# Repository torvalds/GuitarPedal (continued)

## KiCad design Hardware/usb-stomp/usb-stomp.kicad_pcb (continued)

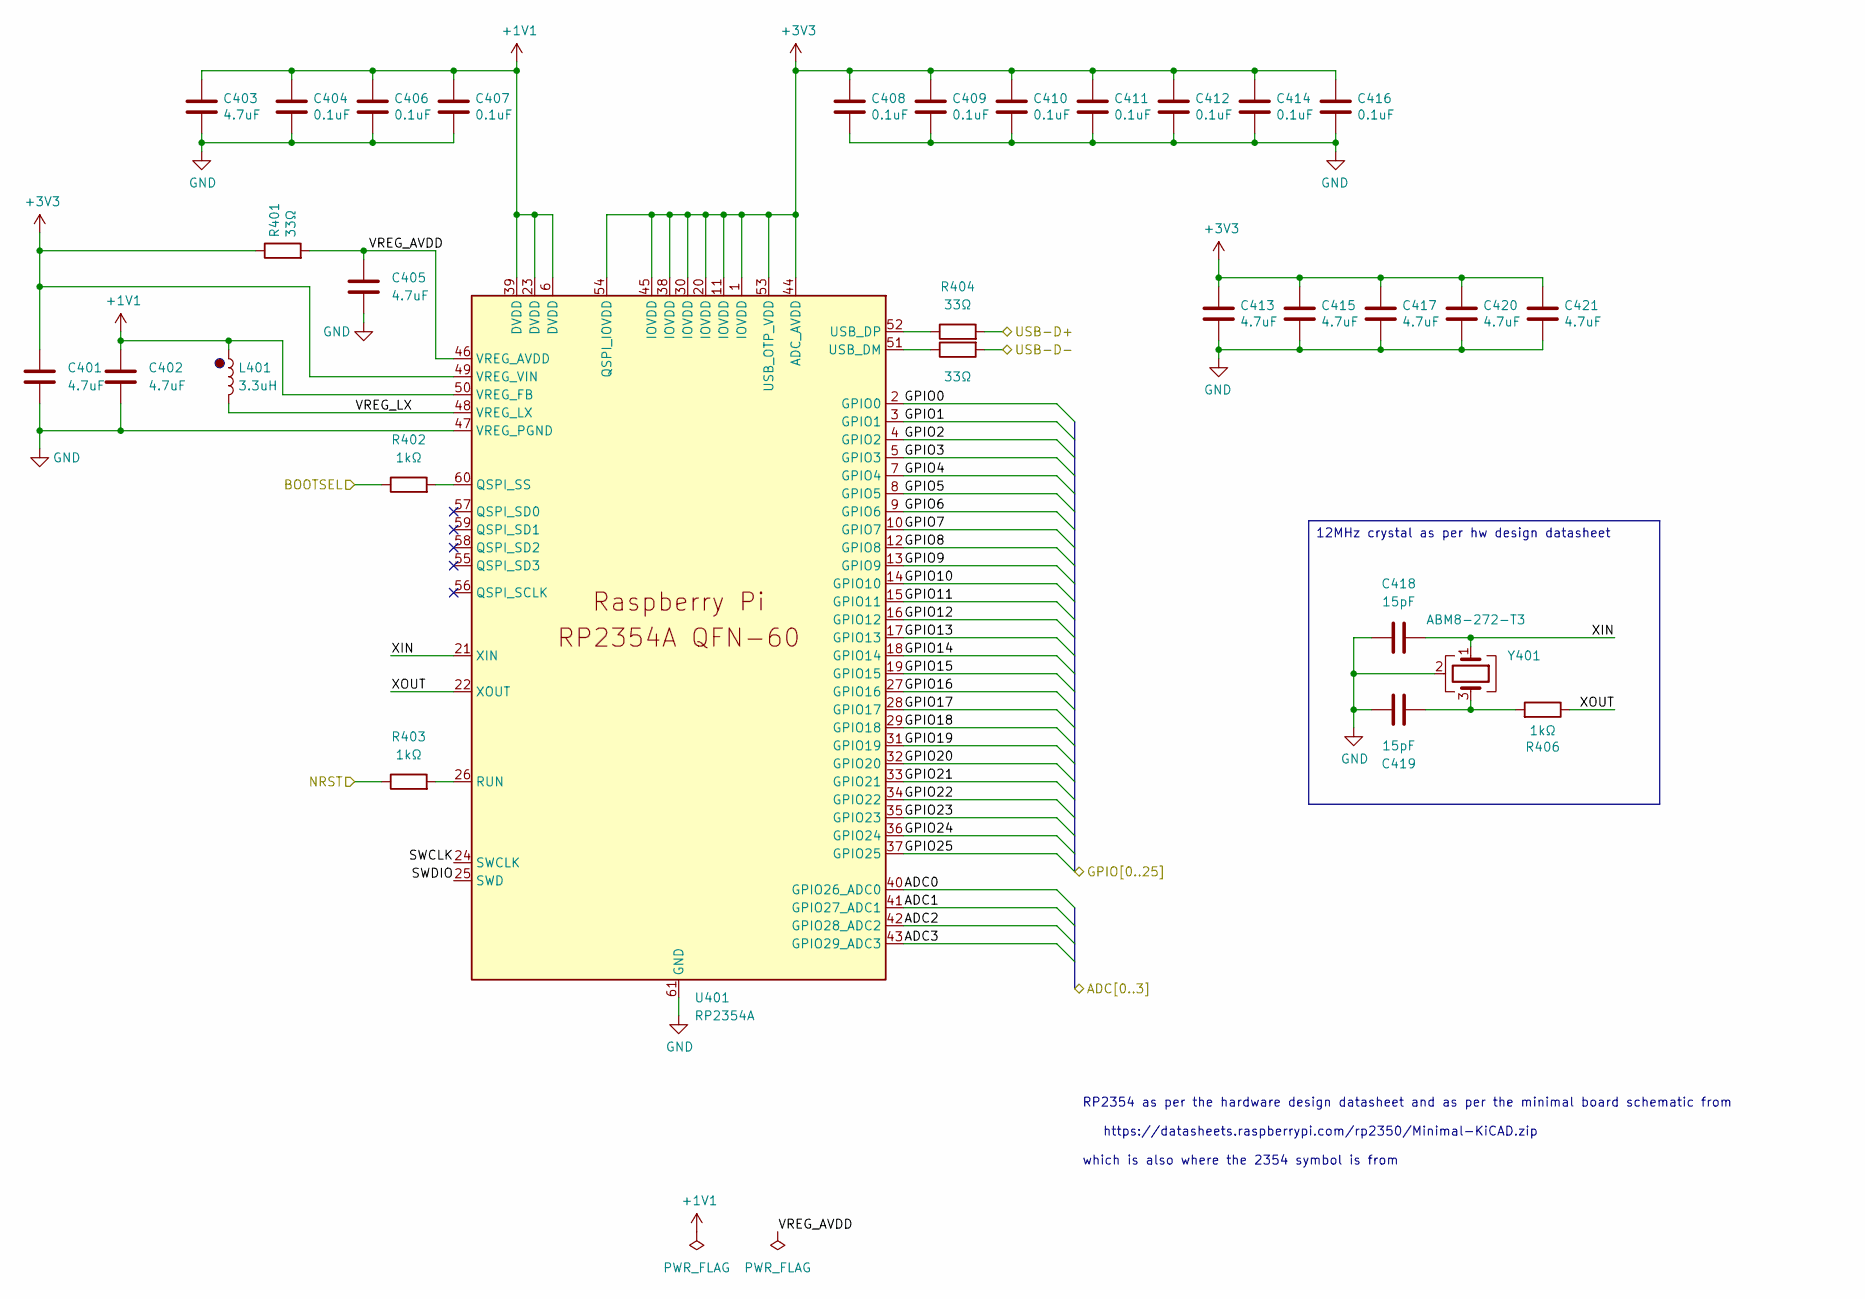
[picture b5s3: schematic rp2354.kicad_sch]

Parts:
C401, C402, C403, C405, C413, C415, C417, C420, C421: 4.7uF; C_0402_1005Metric; MANUFACTURER_PART_NUMBER GRM155R61E475ME15D; LCSC PN C2858031
C404, C406, C407, C408, C409, C410, C411, C412, C414, C416: 0.1uF; C_0402_1005Metric; MANUFACTURER_PART_NUMBER CL05B104KO5NNNC; LCSC PN C1525
C418, C419: 15pF; C_0402_1005Metric; MANUFACTURER_PART_NUMBER GRM1555C1H150JA01D; LCSC PN C76950
L401: 3.3uH; AOTA-B2016; MANUFACTURER_PART_NUMBER AOTA-B201610S3R3-101-T; LCSC PN C42411119
R401, R404, R405: 33Ω; R_0402_1005Metric; MANUFACTURER_PART_NUMBER 0402WGF330JTCE; LCSC PN C25105
R402, R403, R406: 1kΩ; R_0402_1005Metric; MANUFACTURER_PART_NUMBER 0402WGF1001TCE; LCSC PN C11702
U401: RP2354A; QFN-60-1EP_7x7mm_P0.4mm_EP3.4x3.4mm_ThermalVias; MANUFACTURER_PART_NUMBER RP2354A; LCSC PN C41378174
Y401: ABM8-272-T3; Crystal_SMD_3225-4Pin_3.2x2.5mm; MANUFACTURER_PART_NUMBER ABM8-272-T3; LCSC PN C20625731

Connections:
+1V1: C402.1, C403.1, C404.1, C406.1, C407.1, L401.1, U401.6 (DVDD), U401.23 (DVDD), U401.39 (DVDD), U401.50 (VREG_FB)
+3V3: C401.1, C408.1, C409.1, C410.1, C411.1, C412.1, C413.1, C414.1, C415.1, C416.1, C417.1, C420.1, C421.1, R401.1, U401.1 (IOVDD), U401.11 (IOVDD), U401.20 (IOVDD), U401.30 (IOVDD), U401.38 (IOVDD), U401.44 (ADC_AVDD), U401.45 (IOVDD), U401.49 (VREG_VIN), U401.53 (USB_OTP_VDD), U401.54 (QSPI_IOVDD); also elsewhere on the board
/BOOTSEL: R402.1; also elsewhere on the board
/RP2354/ADC0: U401.40 (GPIO26_ADC0); also elsewhere on the board
/RP2354/ADC1: U401.41 (GPIO27_ADC1); also elsewhere on the board
/RP2354/ADC2: U401.42 (GPIO28_ADC2)
/RP2354/ADC3: U401.43 (GPIO29_ADC3)
/RP2354/GPIO0: U401.2 (GPIO0); also elsewhere on the board
/RP2354/GPIO1: U401.3 (GPIO1)
/RP2354/GPIO2: U401.4 (GPIO2)
/RP2354/GPIO3: U401.5 (GPIO3)
/RP2354/GPIO4: U401.7 (GPIO4)
/RP2354/GPIO5: U401.8 (GPIO5)
/RP2354/GPIO6: U401.9 (GPIO6)
/RP2354/GPIO7: U401.10 (GPIO7)
/RP2354/GPIO12: U401.16 (GPIO12); also elsewhere on the board
/RP2354/GPIO13: U401.17 (GPIO13); also elsewhere on the board
/RP2354/GPIO14: U401.18 (GPIO14); also elsewhere on the board
/RP2354/GPIO15: U401.19 (GPIO15)
/RP2354/GPIO16: U401.27 (GPIO16)
/RP2354/GPIO17: U401.28 (GPIO17)
/RP2354/GPIO18: U401.29 (GPIO18)
/RP2354/GPIO19: U401.31 (GPIO19)
/RP2354/GPIO20: U401.32 (GPIO20); also elsewhere on the board
/RP2354/GPIO21: U401.33 (GPIO21); also elsewhere on the board
/RP2354/GPIO22: U401.34 (GPIO22)
/RP2354/GPIO23: U401.35 (GPIO23)
/RP2354/GPIO24: U401.36 (GPIO24)
/RP2354/GPIO25: U401.37 (GPIO25); also elsewhere on the board
/RP2354/NRST: R403.1
/RP2354/SWCLK: U401.24 (SWCLK)
/RP2354/SWDIO: U401.25 (SWD)
/RP2354/VREG_AVDD: C405.1, R401.2, U401.46 (VREG_AVDD)
/RP2354/VREG_LX: L401.2, U401.48 (VREG_LX)
/RP2354/XIN: C418.1, U401.21 (XIN), Y401.1
/RP2354/XOUT: R406.1, U401.22 (XOUT)
/TAC5242/I2S.BCLK: U401.12 (GPIO8); also elsewhere on the board
/TAC5242/I2S.DIN: U401.14 (GPIO10); also elsewhere on the board
/TAC5242/I2S.DOUT: U401.15 (GPIO11); also elsewhere on the board
/TAC5242/I2S.FSYNC: U401.13 (GPIO9); also elsewhere on the board
/USB-D+: R404.2; also elsewhere on the board
/USB-D-: R405.2; also elsewhere on the board
GND: C401.2, C402.2, C403.2, C404.2, C405.2, C406.2, C407.2, C408.2, C409.2, C410.2, C411.2, C412.2, C413.2, C414.2, C415.2, C416.2, C417.2, C418.2, C419.2, C420.2, C421.2, U401.47 (VREG_PGND), U401.61 (GND), Y401.2 (G), Y401.4 (G); also elsewhere on the board
unnamed: C419.1, R406.2, Y401.3
unnamed: R402.2, U401.60 (QSPI_SS)
unnamed: R403.2, U401.26 (RUN)
unnamed: R405.1, U401.51 (USB_DM)
unnamed: R404.1, U401.52 (USB_DP)

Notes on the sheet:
RP2354 as per the hardware design datasheet and as per the minimal board schematic from https://datasheets.raspberrypi.com/rp2350/Minimal-KiCAD.zip which is also where the 2354 symbol is from
12MHz crystal as per hw design datasheet

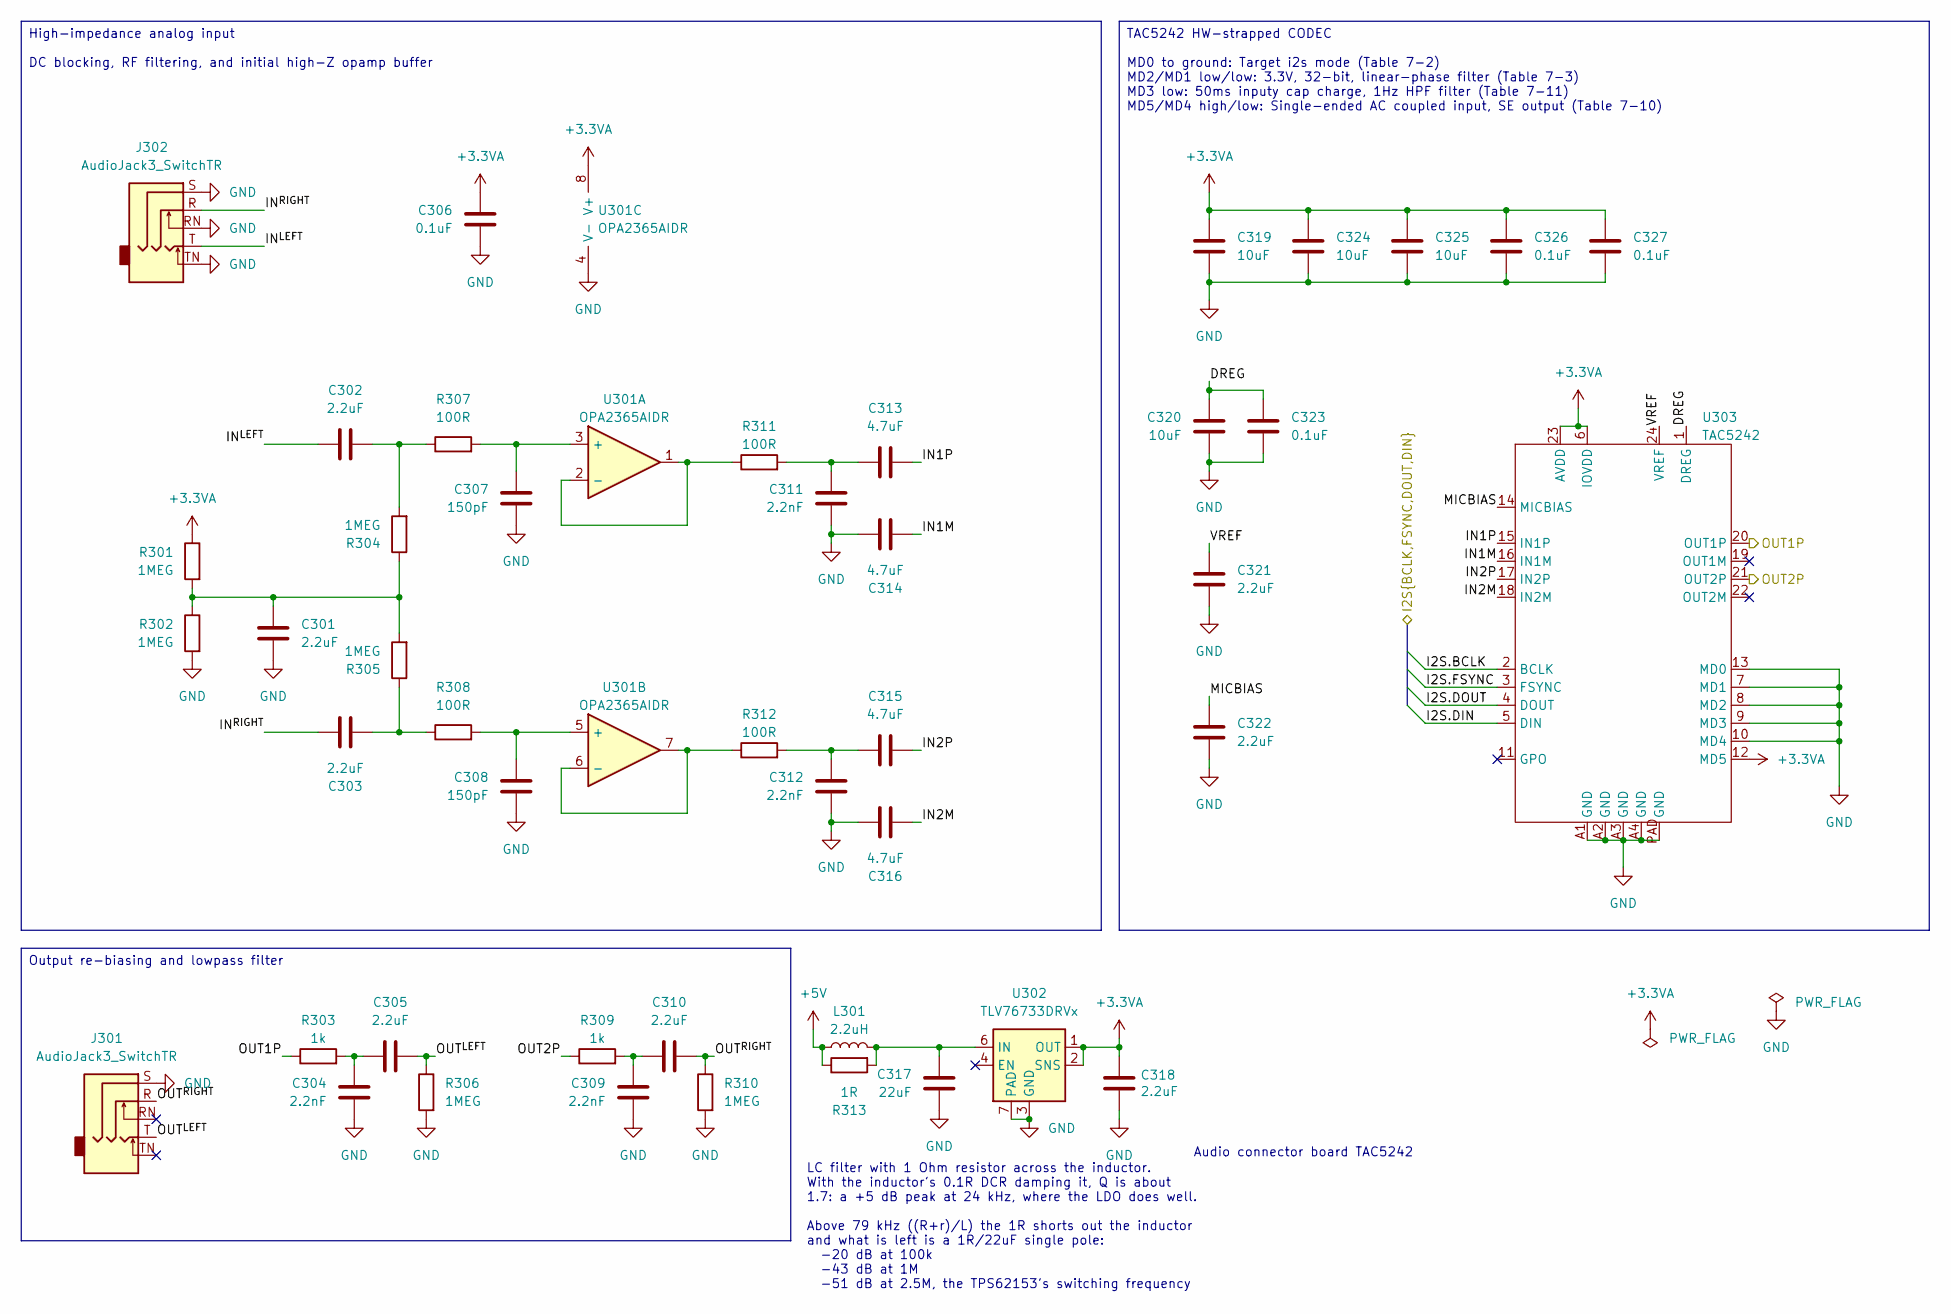
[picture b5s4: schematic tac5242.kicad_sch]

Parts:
C301, C302, C303, C305, C310, C318, C321, C322: 2.2uF; C_0603_1608Metric; MANUFACTURER_PART_NUMBER GRM188Z71E225KE43D; LCSC PN C415535
C304, C309, C311, C312: 2.2nF; C_0402_1005Metric; MANUFACTURER_PART_NUMBER GRM1555C1H222GA01D; LCSC PN C2987940
C306, C323, C326, C327: 0.1uF; C_0402_1005Metric; MANUFACTURER_PART_NUMBER CL05B104KO5NNNC; LCSC PN C1525
C307, C308: 150pF; C_0402_1005Metric; MANUFACTURER_PART_NUMBER GRM1555C1E151JA01D; LCSC PN C710836
C313, C314, C315, C316: 4.7uF; C_0805_2012Metric; MANUFACTURER_PART_NUMBER GRM21BZ71H475KE15L; LCSC PN C437557
C317: 22uF; C_1210_3225Metric; MANUFACTURER_PART_NUMBER CL32B226KAJNNNE; LCSC PN C309062
C319, C320, C324, C325: 10uF; C_0603_1608Metric; MANUFACTURER_PART_NUMBER GRM188R61E106MA73D; LCSC PN C91606
J301, J302: AudioJack3_SwitchTR; NRJ6HM-1-PRE
L301: 2.2uH; L_0806; MANUFACTURER_PART_NUMBER DFE201612E-2R2M=P2; LCSC PN C337893
R301, R302, R304, R305, R306, R310: 1MEG; R_0402_1005Metric; MANUFACTURER_PART_NUMBER MCS04020C1004FE000; LCSC PN C1884615
R303, R309: 1k; R_0402_1005Metric; MANUFACTURER_PART_NUMBER RT0402FRE071KL; LCSC PN C136974
R307, R308, R311, R312: 100R; R_0402_1005Metric; MANUFACTURER_PART_NUMBER RT0402BRD07100RL; LCSC PN C705627
R313: 1R; R_0402_1005Metric; MANUFACTURER_PART_NUMBER FRC0402F1R00TS; LCSC PN C2909329
U301: OPA2365AIDR; SOIC-8_3.9x4.9mm_P1.27mm; MANUFACTURER_PART_NUMBER OPA2365AIDR; LCSC PN C130011
U302: TLV76733DRVx; WSON-6-1EP_2x2mm_P0.65mm_EP1x1.6mm; MANUFACTURER_PART_NUMBER TLV76733DRVR; LCSC PN C2848334
U303: TAC5242; MANUFACTURER_PART_NUMBER TAC5242IRGER; LCSC PN C47122155

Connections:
+3.3VA: C306.2, C318.1, C319.1, C324.1, C325.1, C326.1, C327.1, R301.1, U301.8 (V+), U302.1 (OUT), U302.2 (SNS), U303.6 (IOVDD), U303.12 (MD5), U303.23 (AVDD)
+5V: L301.1, R313.1; also elsewhere on the board
/OUT1P: R303.1, U303.20 (OUT1P)
/OUT2P: R309.1, U303.21 (OUT2P)
/TAC5242/DREG: C320.1, C323.1, U303.1 (DREG)
/TAC5242/I2S.BCLK: U303.2 (BCLK); also elsewhere on the board
/TAC5242/I2S.DIN: U303.5 (DIN); also elsewhere on the board
/TAC5242/I2S.DOUT: U303.4 (DOUT); also elsewhere on the board
/TAC5242/I2S.FSYNC: U303.3 (FSYNC); also elsewhere on the board
/TAC5242/IN1M: C314.2, U303.16 (IN1M)
/TAC5242/IN1P: C313.2, U303.15 (IN1P)
/TAC5242/IN2M: C316.2, U303.18 (IN2M)
/TAC5242/IN2P: C315.2, U303.17 (IN2P)
/TAC5242/IN^{LEFT}: C302.1, J302.T
/TAC5242/IN^{RIGHT}: C303.1, J302.R
/TAC5242/MICBIAS: C322.1, U303.14 (MICBIAS)
/TAC5242/OUT^{LEFT}: C305.2, J301.T, R306.1
/TAC5242/OUT^{RIGHT}: C310.2, J301.R, R310.1
/TAC5242/VREF: C321.1, U303.24 (VREF)
GND: C301.1, C304.1, C306.1, C307.2, C308.2, C309.1, C311.1, C312.1, C314.1, C316.1, C317.2, C318.2, C319.2, C320.2, C321.2, C322.2, C323.2, C324.2, C325.2, C326.2, C327.2, J301.S, J302.RN, J302.S, J302.TN, R302.2, R306.2, R310.2, U301.4 (V-), U302.3 (GND), U302.5 (GND), U302.7 (PAD), U303.7 (MD1), U303.8 (MD2), U303.9 (MD3), U303.10 (MD4), U303.13 (MD0), U303.A1 (GND), U303.A2 (GND), U303.A3 (GND), U303.A4 (GND), U303.PAD (GND); also elsewhere on the board
unnamed: C301.2, R301.2, R302.1, R304.1, R305.2
unnamed: C302.2, R304.2, R307.1
unnamed: C303.2, R305.1, R308.1
unnamed: C304.2, C305.1, R303.2
unnamed: C309.2, C310.1, R309.2
unnamed: C311.2, C313.1, R311.2
unnamed: C312.2, C315.1, R312.2
unnamed: C307.1, R307.2, U301.3 (+)
unnamed: R311.1, U301.1, U301.2 (-)
unnamed: C308.1, R308.2, U301.5 (+)
unnamed: R312.1, U301.6 (-), U301.7
unnamed: C317.1, L301.2, R313.2, U302.6 (IN)

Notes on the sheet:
LC filter with 1 Ohm resistor across the inductor. With the inductor's 0.1R DCR damping it, Q is about 1.7: a +5 dB peak at 24 kHz, where the LDO does well. Above 79 kHz ((R+r)/L) the 1R shorts out the inductor and what is left is a 1R/22uF single pole: -20 dB at 100k -43 dB at 1M -51 dB at 2.5M, t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
Audio connector board TAC5242
High-impedance analog input DC blocking, RF filtering, and initial high-Z opamp buffer
Output re-biasing and lowpass filter
TAC5242 HW-strapped CODEC MD0 to ground: Target i2s mode (Table 7-2) MD2/MD1 low/low: 3.3V, 32-bit, linear-phase filter (Table 7-3) MD3 low: 50ms inputy cap charge, 1Hz HPF filter (Table 7-11) MD5/MD4 high/low: Single-ended AC coupled input, SE output (Table 7-10)

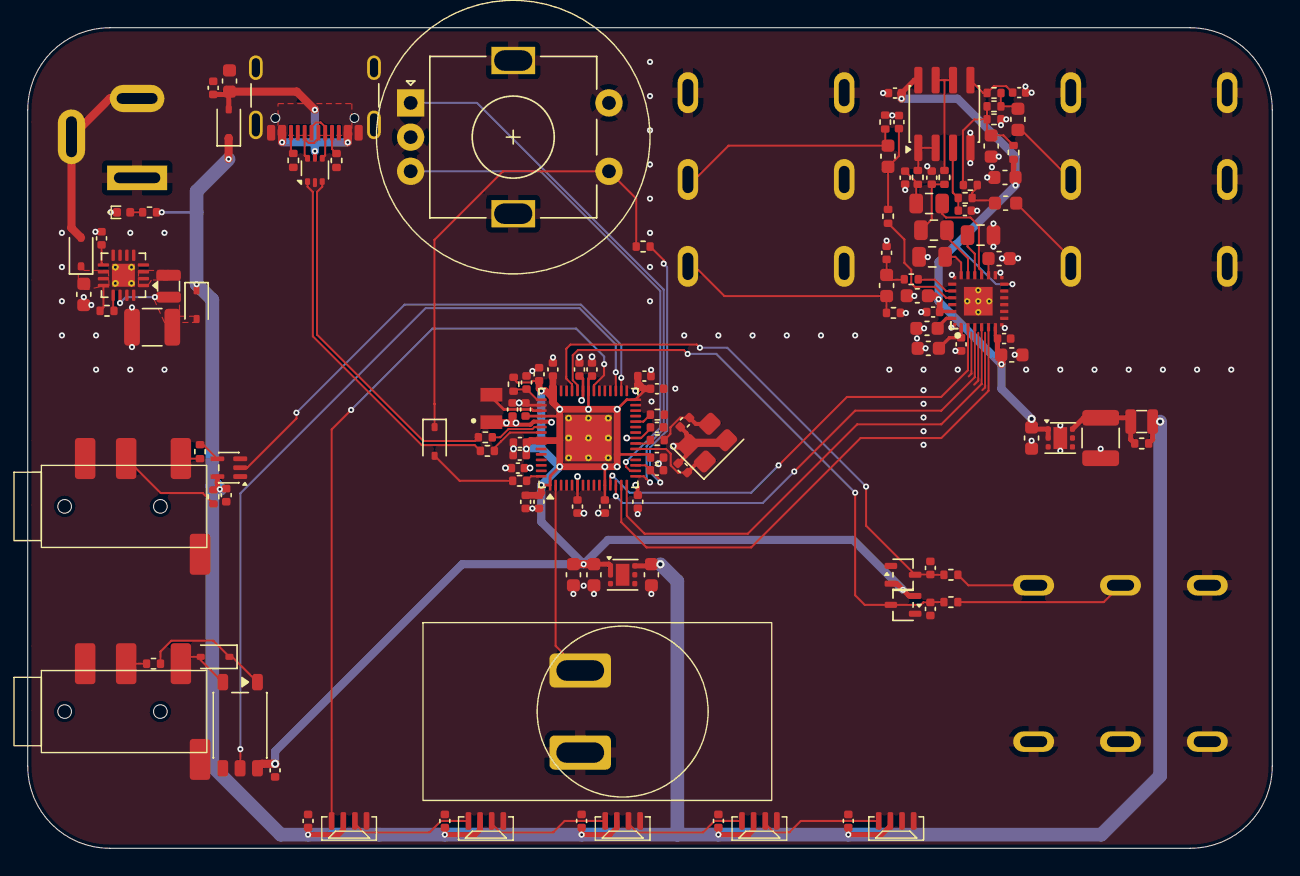
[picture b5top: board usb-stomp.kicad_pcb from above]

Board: 4 copper layers, 91.0 x 60.0 mm, 130 parts (0 on the bottom side), 80 nets.

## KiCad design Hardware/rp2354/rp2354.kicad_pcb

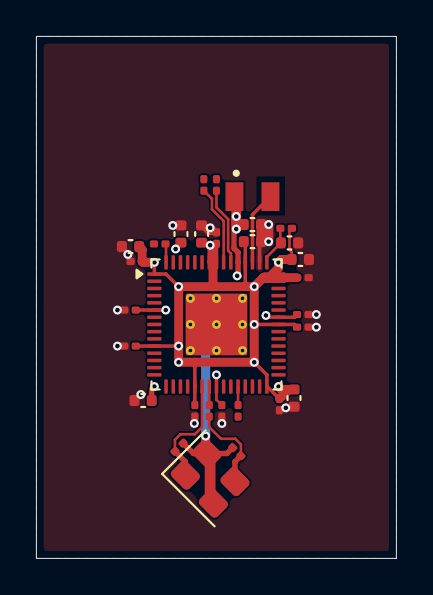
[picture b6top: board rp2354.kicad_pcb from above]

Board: 4 copper layers, 20.0 x 29.0 mm, 30 parts (0 on the bottom side), 12 nets.

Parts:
C1, C2, C3, C5, C17, C18, C19, C20, C21: 4.7uF; C_0402_1005Metric
C4, C6, C7, C8, C9, C10, C11, C12, C13, C14: 0.1uF; C_0201_0603Metric
C15, C16: 15pF; C_0201_0603Metric
L1: 3.3uH; AOTA-B2016
R1, R4, R5: 33R; R_0201_0603Metric
R2, R3, R6: 1k; R_0201_0603Metric
U1: RP2354A; QFN-60-1EP_7x7mm_P0.4mm_EP3.4x3.4mm_ThermalVias
Y1: ABM8-272-T3; Crystal_SMD_3225-4Pin_3.2x2.5mm

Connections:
+1V1: C2.1, C3.1, C4.1, C6.1, C7.1, L1.1, U1.6 (DVDD), U1.23 (DVDD), U1.39 (DVDD), U1.50 (VREG_FB)
+3V3: C1.1, C8.1, C9.1, C10.1, C11.1, C12.1, C13.1, C14.1, C17.1, C18.1, C19.1, C20.1, C21.1, R1.1, U1.1 (IOVDD), U1.11 (IOVDD), U1.20 (IOVDD), U1.30 (IOVDD), U1.38 (IOVDD), U1.44 (ADC_AVDD), U1.45 (IOVDD), U1.49 (VREG_VIN), U1.53 (USB_OTP_VDD), U1.54 (QSPI_IOVDD)
/VREG_AVDD: C5.1, R1.2, U1.46 (VREG_AVDD)
/VREG_LX: L1.2, U1.48 (VREG_LX)
/XIN: C15.1, U1.21 (XIN), Y1.1
/XOUT: R6.1, U1.22 (XOUT)
GND: C1.2, C2.2, C3.2, C4.2, C5.2, C6.2, C7.2, C8.2, C9.2, C10.2, C11.2, C12.2, C13.2, C14.2, C15.2, C16.2, C17.2, C18.2, C19.2, C20.2, C21.2, U1.47 (VREG_PGND), U1.61 (GND), Y1.2 (G), Y1.4 (G)
unnamed: C16.1, R6.2, Y1.3
unnamed: R2.2, U1.60 (QSPI_SS)
unnamed: R3.2, U1.26 (RUN)
unnamed: R5.1, U1.51 (USB_DM)
unnamed: R4.1, U1.52 (USB_DP)

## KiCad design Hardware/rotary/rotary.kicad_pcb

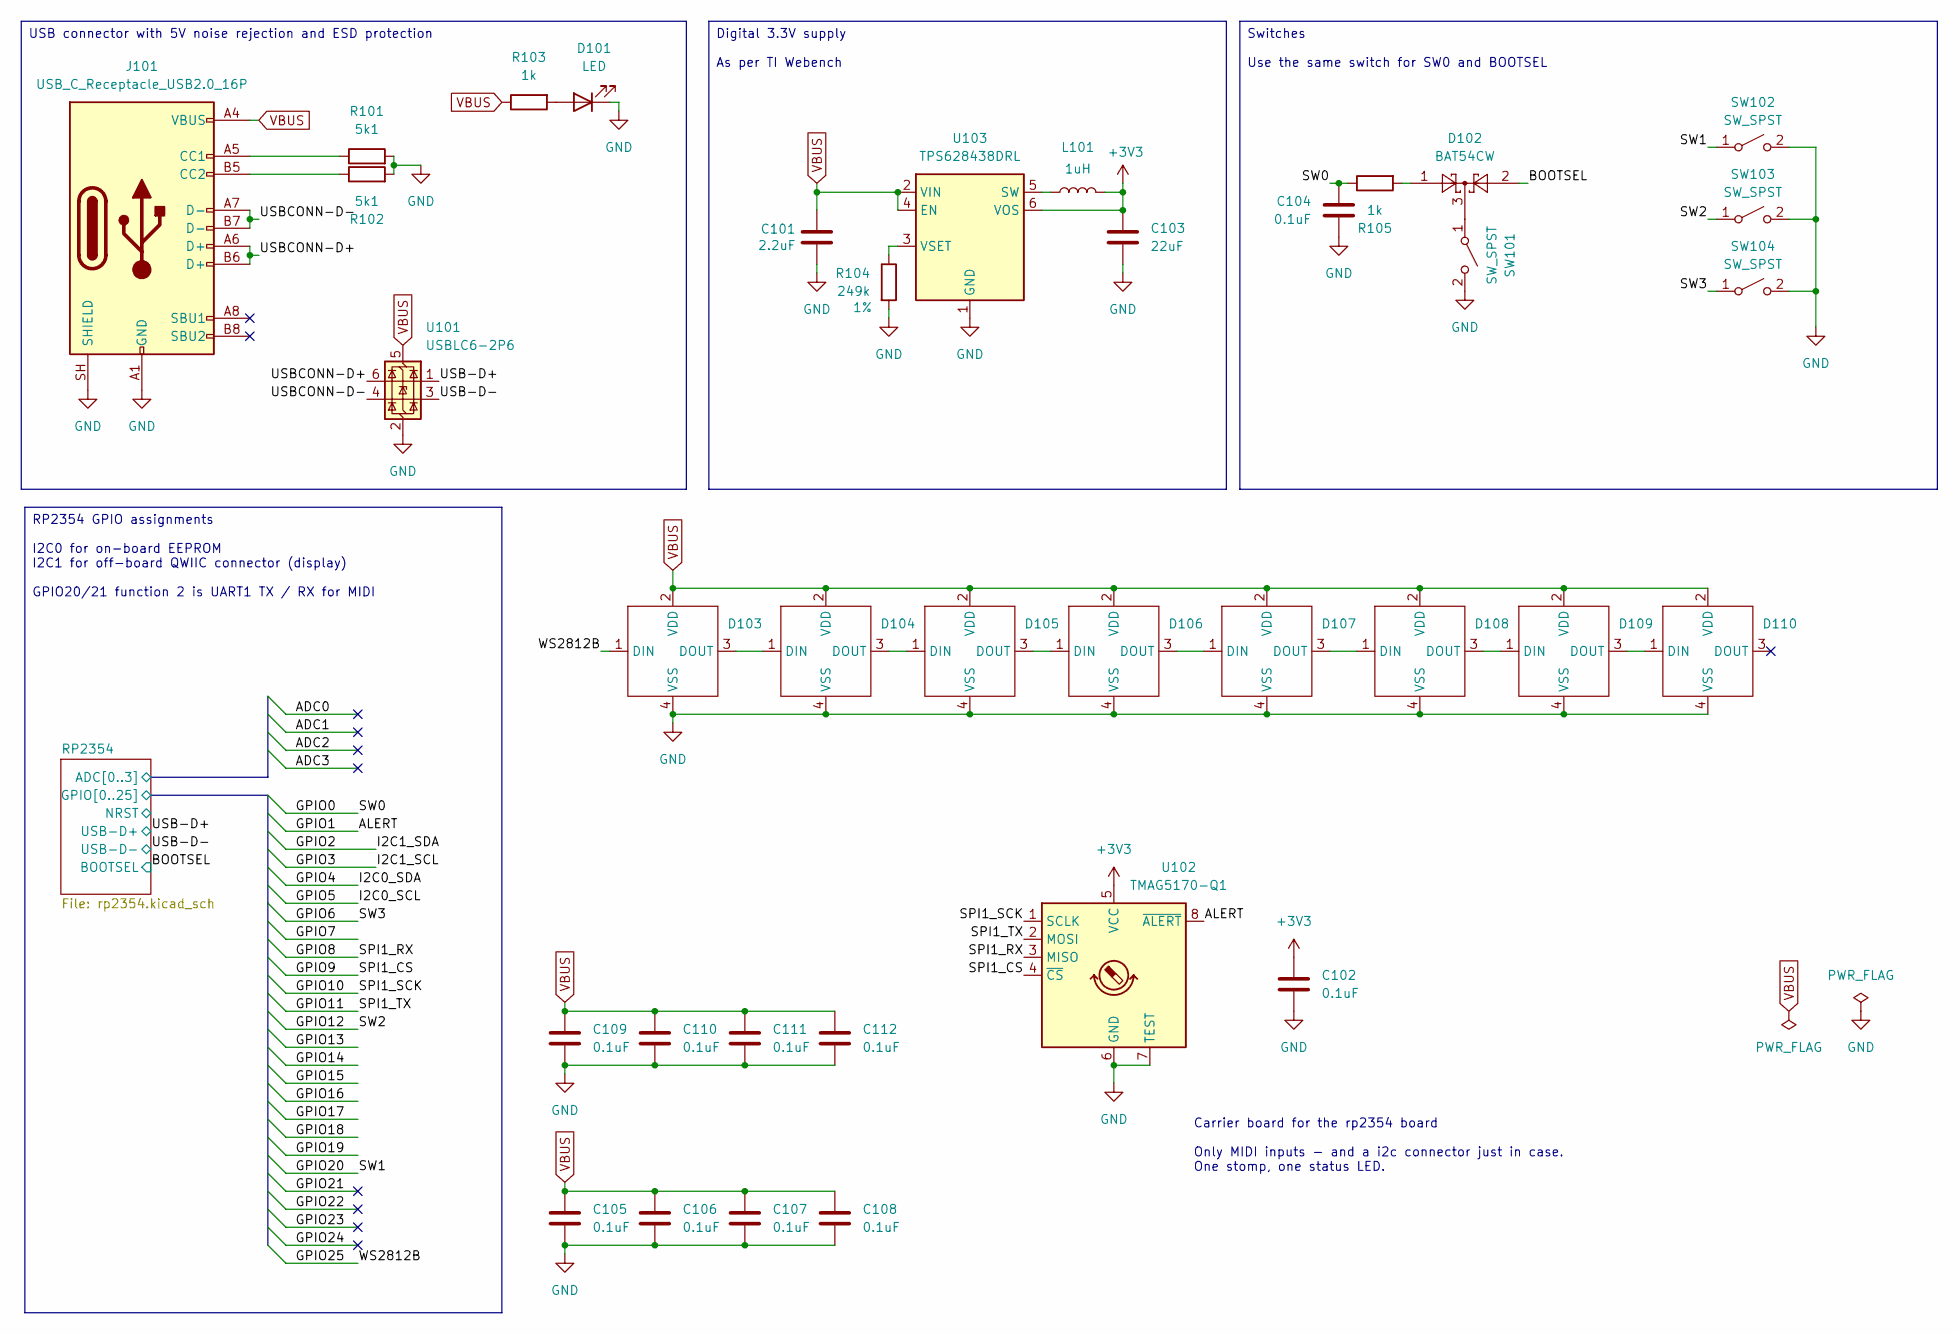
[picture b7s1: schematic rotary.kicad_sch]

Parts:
C101: 2.2uF; C_0603_1608Metric; LCSC PN C415535
C102, C104, C105, C106, C107, C108, C109, C110, C111, C112: 0.1uF; C_0201_0603Metric; LCSC PN C3901090
C103: 22uF; C_0805_2012Metric; LCSC PN C86816
D101: LED; LED_0402_1005Metric; LCSC PN C160479
D102: BAT54CW; SOT-323_SC-70; LCSC PN C22392482
D103, D104, D105, D106, D107, D108, D109, D110: WS2812B-4020; LCSC PN C965557
J101: USB_C_Receptacle_USB2.0_16P; USB_C_Receptacle_GCT_USB4105-xx-A_16P_TopMnt_Horizontal; LCSC PN C2843967
L101: 1uH; L_0806; Part# LQM2MPN1R0MGHL; LCSC PN C528977
R101, R102: 5k1; R_0201_0603Metric; LCSC PN C270344
R103, R105: 1k; R_0201_0603Metric; LCSC PN C270365
R104: 249k; R_0201_0603Metric; LCSC PN C273273
SW101, SW102, SW103, SW104: SW_SPST; ZX-QC1212; MANUFACTURER_PART_NUMBER ZX-QC1212-4.3TP; LCSC PN C7470196
U101: USBLC6-2P6; SOT-666; LCSC PN C15999
U102: TMAG5170-Q1; VSSOP-8_3x3mm_P0.65mm; LCSC PN C5220642
U103: TPS628438DRL; SOT-563; LCSC PN C38060243

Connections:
+3V3: C102.2, C103.1, L101.2, U102.5 (VCC), U103.6 (VOS); also elsewhere on the board
/BOOTSEL: D102.2; also elsewhere on the board
/RP2354/GPIO0: C104.2, R105.1; also elsewhere on the board
/RP2354/GPIO1: U102.8 (~ALERT); also elsewhere on the board
/RP2354/GPIO6: SW104.1 (A); also elsewhere on the board
/RP2354/GPIO8: U102.3 (MISO); also elsewhere on the board
/RP2354/GPIO9: U102.4 (~CS); also elsewhere on the board
/RP2354/GPIO10: U102.1 (SCLK); also elsewhere on the board
/RP2354/GPIO11: U102.2 (MOSI); also elsewhere on the board
/RP2354/GPIO12: SW103.1 (A); also elsewhere on the board
/RP2354/GPIO20: SW102.1 (A); also elsewhere on the board
/RP2354/GPIO25: D103.1 (DIN); also elsewhere on the board
/USB-D+: U101.1 (I/O1); also elsewhere on the board
/USB-D-: U101.3 (I/O2); also elsewhere on the board
/USBCONN-D+: J101.A6 (D+), J101.B6 (D+), U101.6 (I/O1)
/USBCONN-D-: J101.A7 (D-), J101.B7 (D-), U101.4 (I/O2)
GND: C101.2, C102.1, C103.2, C104.1, C105.1, C106.1, C107.1, C108.1, C109.1, C110.1, C111.1, C112.1, D101.1 (K), D103.4 (VSS), D104.4 (VSS), D105.4 (VSS), D106.4 (VSS), D107.4 (VSS), D108.4 (VSS), D109.4 (VSS), D110.4 (VSS), J101.A1 (GND), J101.A12 (GND), J101.B1 (GND), J101.B12 (GND), J101.SH (SHIELD), R101.2, R102.2, R104.2, SW101.2 (B), SW102.2 (B), SW103.2 (B), SW104.2 (B), U101.2 (GND), U102.6 (GND), U102.7 (TEST), U103.1 (GND); also elsewhere on the board
unnamed: D101.2 (A), R103.2
unnamed: D102.1, R105.2
unnamed: D103.3 (DOUT), D104.1 (DIN)
unnamed: D104.3 (DOUT), D105.1 (DIN)
unnamed: D105.3 (DOUT), D106.1 (DIN)
unnamed: D106.3 (DOUT), D107.1 (DIN)
unnamed: D107.3 (DOUT), D108.1 (DIN)
unnamed: D108.3 (DOUT), D109.1 (DIN)
unnamed: D109.3 (DOUT), D110.1 (DIN)
unnamed: J101.A5 (CC1), R101.1
unnamed: J101.B5 (CC2), R102.1
unnamed: D102.3, SW101.1 (A)
unnamed: L101.1, U103.5 (SW)
unnamed: R104.1, U103.3 (VSET)
VBUS: C101.1, C105.2, C106.2, C107.2, C108.2, C109.2, C110.2, C111.2, C112.2, D103.2 (VDD), D104.2 (VDD), D105.2 (VDD), D106.2 (VDD), D107.2 (VDD), D108.2 (VDD), D109.2 (VDD), D110.2 (VDD), J101.A4 (VBUS), J101.A9 (VBUS), J101.B4 (VBUS), J101.B9 (VBUS), R103.1, U101.5 (VBUS), U103.2 (VIN), U103.4 (EN)

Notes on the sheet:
Carrier board for the rp2354 board Only MIDI inputs - and a i2c connector just in case. One stomp, one status LED.
Switches Use the same switch for SW0 and BOOTSEL
RP2354 GPIO assignments I2C0 for on-board EEPROM I2C1 for off-board QWIIC connector (display) GPIO20/21 function 2 is UART1 TX / RX for MIDI
Digital 3.3V supply As per TI Webench
USB connector with 5V noise rejection and ESD protection

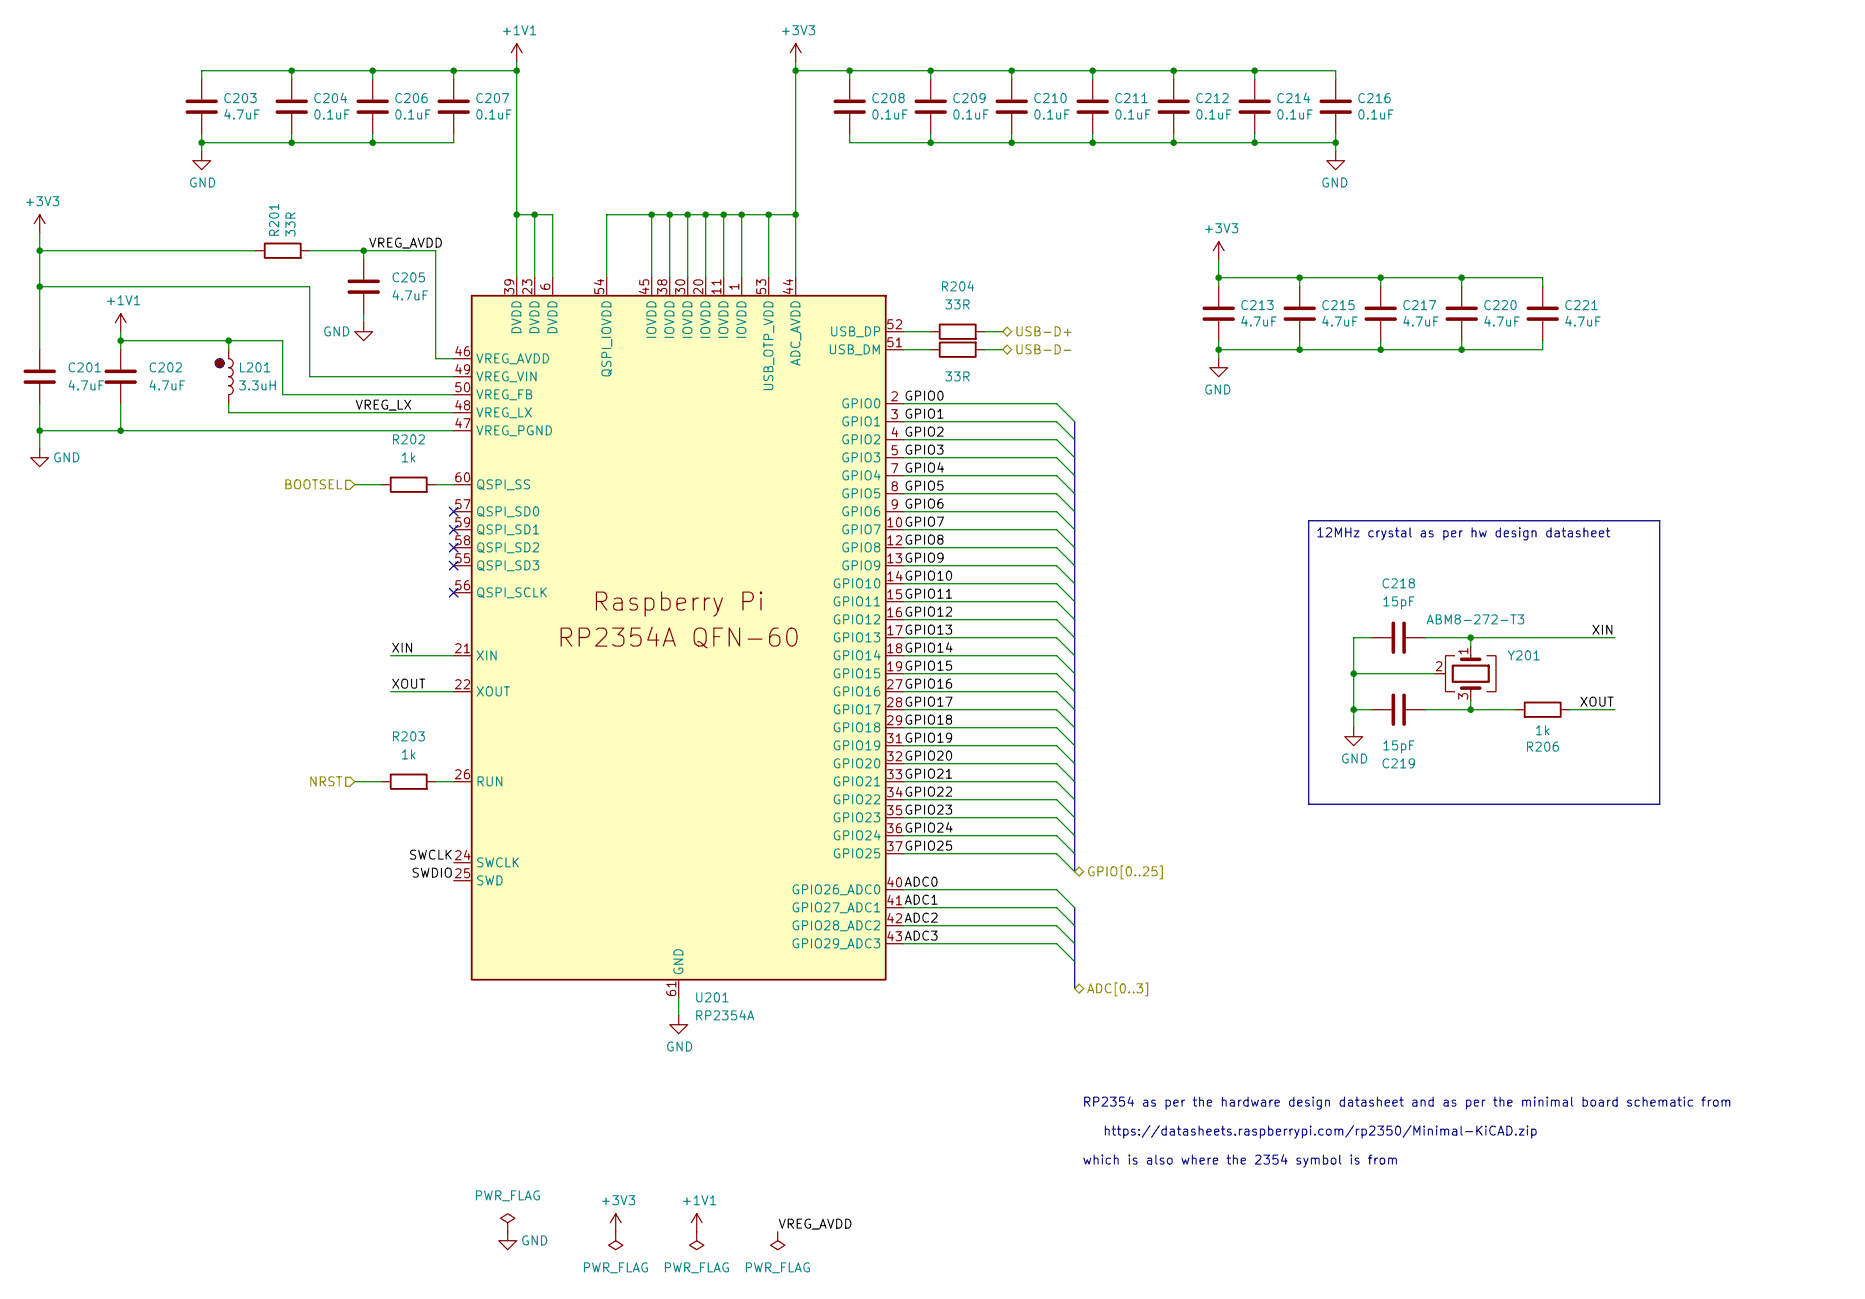
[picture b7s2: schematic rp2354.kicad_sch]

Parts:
C201, C202, C203, C205, C213, C215, C217, C220, C221: 4.7uF; C_0402_1005Metric; LCSC PN C2858031
C204, C206, C207, C208, C209, C210, C211, C212, C214, C216: 0.1uF; C_0201_0603Metric; LCSC PN C3901090
C218, C219: 15pF; C_0201_0603Metric; LCSC PN C161373
L201: 3.3uH; AOTA-B2016; LCSC PN C42411119
R201, R204, R205: 33R; R_0201_0603Metric; LCSC PN C423356
R202, R203, R206: 1k; R_0201_0603Metric; LCSC PN C270365
U201: RP2354A; QFN-60-1EP_7x7mm_P0.4mm_EP3.4x3.4mm_ThermalVias; LCSC PN C41378174
Y201: ABM8-272-T3; Crystal_SMD_3225-4Pin_3.2x2.5mm; LCSC PN C20625731

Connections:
+1V1: C202.1, C203.1, C204.1, C206.1, C207.1, L201.1, U201.6 (DVDD), U201.23 (DVDD), U201.39 (DVDD), U201.50 (VREG_FB)
+3V3: C201.1, C208.1, C209.1, C210.1, C211.1, C212.1, C213.1, C214.1, C215.1, C216.1, C217.1, C220.1, C221.1, R201.1, U201.1 (IOVDD), U201.11 (IOVDD), U201.20 (IOVDD), U201.30 (IOVDD), U201.38 (IOVDD), U201.44 (ADC_AVDD), U201.45 (IOVDD), U201.49 (VREG_VIN), U201.53 (USB_OTP_VDD), U201.54 (QSPI_IOVDD); also elsewhere on the board
/BOOTSEL: R202.1; also elsewhere on the board
/RP2354/ADC0: U201.40 (GPIO26_ADC0)
/RP2354/ADC1: U201.41 (GPIO27_ADC1)
/RP2354/ADC2: U201.42 (GPIO28_ADC2)
/RP2354/ADC3: U201.43 (GPIO29_ADC3)
/RP2354/GPIO0: U201.2 (GPIO0); also elsewhere on the board
/RP2354/GPIO1: U201.3 (GPIO1); also elsewhere on the board
/RP2354/GPIO2: U201.4 (GPIO2)
/RP2354/GPIO3: U201.5 (GPIO3)
/RP2354/GPIO4: U201.7 (GPIO4)
/RP2354/GPIO5: U201.8 (GPIO5)
/RP2354/GPIO6: U201.9 (GPIO6); also elsewhere on the board
/RP2354/GPIO7: U201.10 (GPIO7)
/RP2354/GPIO8: U201.12 (GPIO8); also elsewhere on the board
/RP2354/GPIO9: U201.13 (GPIO9); also elsewhere on the board
/RP2354/GPIO10: U201.14 (GPIO10); also elsewhere on the board
/RP2354/GPIO11: U201.15 (GPIO11); also elsewhere on the board
/RP2354/GPIO12: U201.16 (GPIO12); also elsewhere on the board
/RP2354/GPIO13: U201.17 (GPIO13)
/RP2354/GPIO14: U201.18 (GPIO14)
/RP2354/GPIO15: U201.19 (GPIO15)
/RP2354/GPIO16: U201.27 (GPIO16)
/RP2354/GPIO17: U201.28 (GPIO17)
/RP2354/GPIO18: U201.29 (GPIO18)
/RP2354/GPIO19: U201.31 (GPIO19)
/RP2354/GPIO20: U201.32 (GPIO20); also elsewhere on the board
/RP2354/GPIO21: U201.33 (GPIO21)
/RP2354/GPIO22: U201.34 (GPIO22)
/RP2354/GPIO23: U201.35 (GPIO23)
/RP2354/GPIO24: U201.36 (GPIO24)
/RP2354/GPIO25: U201.37 (GPIO25); also elsewhere on the board
/RP2354/NRST: R203.1
/RP2354/SWCLK: U201.24 (SWCLK)
/RP2354/SWDIO: U201.25 (SWD)
/RP2354/VREG_AVDD: C205.1, R201.2, U201.46 (VREG_AVDD)
/RP2354/VREG_LX: L201.2, U201.48 (VREG_LX)
/RP2354/XIN: C218.1, U201.21 (XIN), Y201.1
/RP2354/XOUT: R206.1, U201.22 (XOUT)
/USB-D+: R204.2; also elsewhere on the board
/USB-D-: R205.2; also elsewhere on the board
GND: C201.2, C202.2, C203.2, C204.2, C205.2, C206.2, C207.2, C208.2, C209.2, C210.2, C211.2, C212.2, C213.2, C214.2, C215.2, C216.2, C217.2, C218.2, C219.2, C220.2, C221.2, U201.47 (VREG_PGND), U201.61 (GND), Y201.2 (G), Y201.4 (G); also elsewhere on the board
unnamed: C219.1, R206.2, Y201.3
unnamed: R202.2, U201.60 (QSPI_SS)
unnamed: R203.2, U201.26 (RUN)
unnamed: R205.1, U201.51 (USB_DM)
unnamed: R204.1, U201.52 (USB_DP)

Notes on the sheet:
RP2354 as per the hardware design datasheet and as per the minimal board schematic from https://datasheets.raspberrypi.com/rp2350/Minimal-KiCAD.zip which is also where the 2354 symbol is from
12MHz crystal as per hw design datasheet

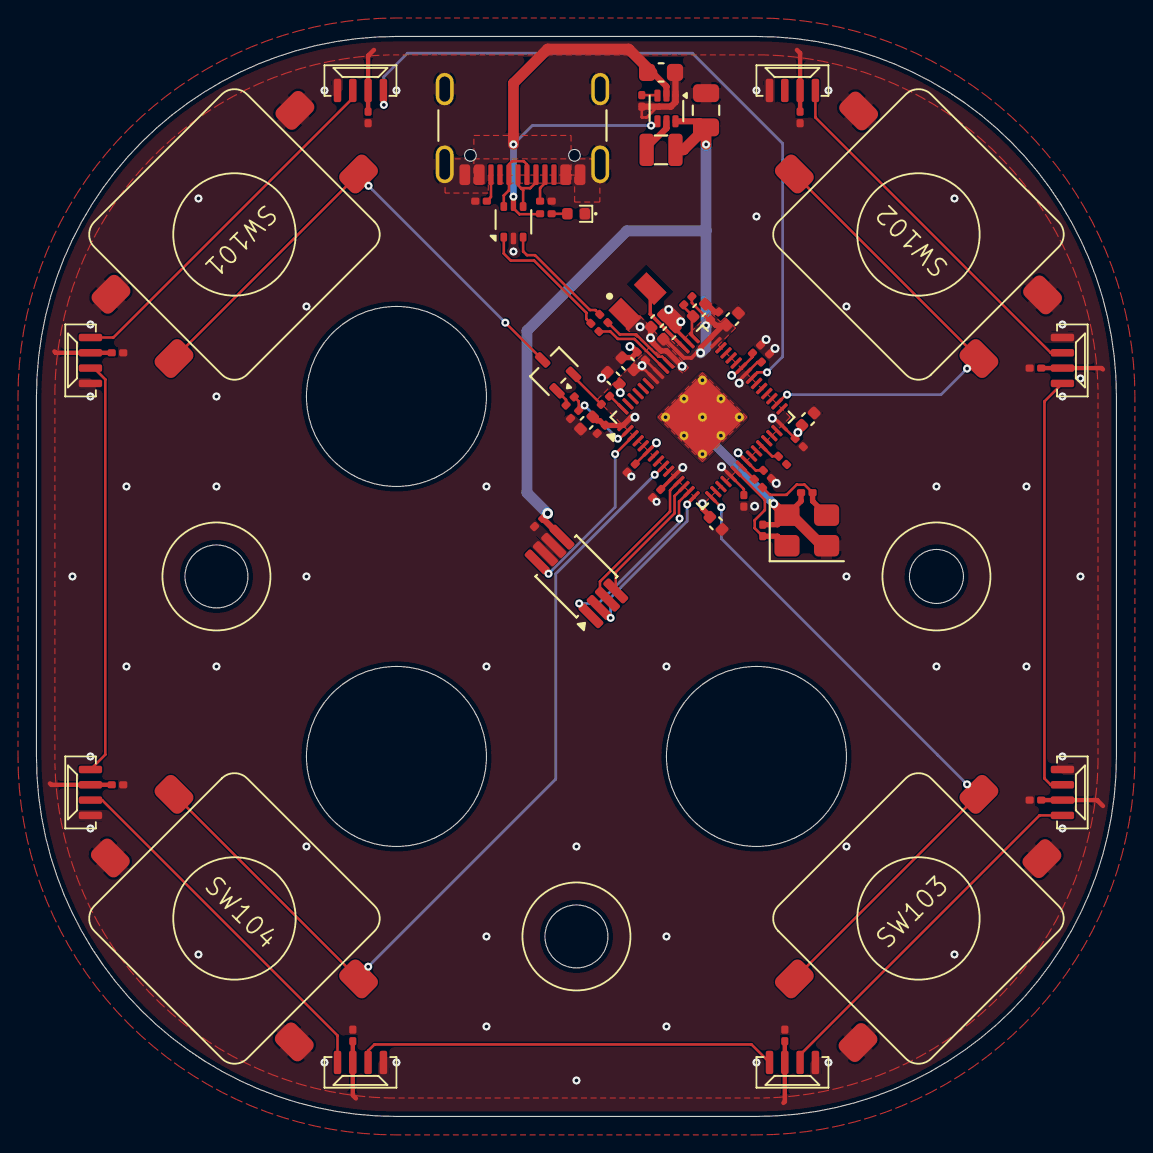
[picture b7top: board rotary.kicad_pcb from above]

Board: 4 copper layers, 60.0 x 60.0 mm, 66 parts (0 on the bottom side), 42 nets.
